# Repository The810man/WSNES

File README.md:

# WSNES „SNES-LoROM-Flashcart mit WLAN-Upload für Homebrew und Entwicklung auf echter Hardware.“

AI NOTICE: Hey so i use claude code for making my commits cleaner sometimes, also for release taggin. Code, pcb and CAD is hand made but also enhanced via mcp tools (for example checking routing and fixing issues like via placement etc.). Agentic workflows used for documentation and versioning.

WSNES is a SNES flash cartridge built around an **ESP32-S3** and parallel SRAM:

- The ESP loads a game from **microSD**, or one uploaded over **WiFi**, into SRAM.
- The SNES then reads that SRAM as a normal **LoROM** cartridge.
- Saves sit in a battery-backed SRAM and are backed up to the SD card.

The board uses the standard SNES cartridge PCB outline, so it fits a custom PAL / Super Famicom style housing.

## Status

**Latest release: [v0.3.2](https://github.com/The810man/WSNES/releases/tag/v0.3.2) (2026-11-17)**, with the gerbers and JLC files as release downloads. See [CHANGELOG.md](CHANGELOG.md).

| Part | State |
| --- | --- |
| Hardware v0.3 | Schematic done (ERC: 0 errors), all 90 parts placed, **fully routed, DRC clean** (KiCad 10.0.8: 0 errors, 0 unconnected, parity 0) |
| Production review | [2026-11-17](docs/reviews/2026-11-17_production-review.md): the tab-copper blocker and the missing USB ESD are **fixed and verified**. Every JLC line has an LCSC number. U1 and U13 were out of stock on 2026-11-17, and two bench checks are still open. See [`pcb/README.md`](pcb/README.md#before-ordering). |
| Production files | Gerbers in `pcb/production/jlc/`. JLC assembly as the full variant (`jlc/`) or the cheap prototype variant (`jlc-cheap/`, with a hand-assembly list) |
| Hardware v0.4 | In progress on `hw/v0.4`: schematic split into 9 sheets, U1/U5/U13 replaced by in-stock parts, two-sided placement, power pre-routed into the planes, net classes for hand routing. **Signal routing is being redone by hand.** See [`pcb/README.md`](pcb/README.md#routing-v04). |
| Housing | First draft: `cad/Cardridge.FCStd` (FreeCAD) |
| Firmware | Not in this repo yet |

## Repository layout

```
.
├── pcb/                    KiCad project (open WSNES_Proto.kicad_pro; the board needs KiCad 10)
│   ├── README.md           board details: who solders what, routing, ordering
│   ├── lib/                project symbols + footprints (cart edge drawn from scratch), vendor 3D models
│   ├── tools/              Python generators; design.py is the design table
│   ├── freerouting/        Specctra DSN for the autorouter
│   └── production/         full BOM, gerbers + JLCPCB assembly files (jlc/), cheap variant (jlc-cheap/)
├── cad/
│   ├── Cardridge.FCStd     first housing draft (FreeCAD)
│   ├── WSNES.step / .stl   latest KiCad 3D export of the board with all parts
│   └── WSNES_Proto.step / .stl   earlier export of the same board
├── docs/
│   ├── reviews/            design reviews (production review 2026-11-17)
│   ├── WSNES_Proto_schematic.pdf   schematic incl. bus map, GPIO map, firmware flow
│   └── masterplan.md               original architecture notes (German, historical)
├── analysis/               review evidence: deep_review.json + helper scripts (analyzer runs are not committed)
├── CHANGELOG.md            release history
├── LICENSES/               full licence texts
├── LICENSE.md              which licence covers what
└── CONTRIBUTING.md         terms for contributions
```

Start with [`pcb/README.md`](pcb/README.md) for the hardware.

## Tools

- KiCad 10 to open the board: `WSNES_Proto.kicad_pcb` is saved in KiCad 10 format, and KiCad 9 can't load it. The schematic still opens in KiCad 9.
- `kicad-cli` and the `pcbnew` Python module, for the generators in `pcb/tools/`
- freerouting, for autorouting
- Python 3

## Research references

These projects were studied while designing WSNES. None of their files are included here.

- [mrehkopf/sd2snes](https://github.com/mrehkopf/sd2snes): FPGA-based SNES flashcart
- [soniccd123/SNES-FeRAM-Cart](https://github.com/soniccd123/SNES-FeRAM-Cart): SNES cart with modern 3.3 V memory
- [MouseBiteLabs/Super-Nintendo-Cartridges](https://github.com/MouseBiteLabs/Super-Nintendo-Cartridges): open SNES cartridge PCBs

## Licence

WSNES is free for non-commercial use: it may be built, modified and shared, but selling it requires the author's permission.

- Hardware and docs: [CC BY-NC-SA 4.0](LICENSES/CC-BY-NC-SA-4.0.txt)
- Code: [PolyForm Noncommercial 1.0.0](LICENSES/PolyForm-Noncommercial-1.0.0.md)

See [LICENSE.md](LICENSE.md) for what counts as non-commercial, and [CONTRIBUTING.md](CONTRIBUTING.md) before sending changes.

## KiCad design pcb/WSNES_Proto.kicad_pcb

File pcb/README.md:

# WSNES Cart v0.4 (work in progress): mixed SMD/THT, two-sided, standard SNES PCB shape

v0.4 fits the standard SNES cartridge PCB outline: 112.2 × 66.7 mm plus the 11.1 mm contact tab, 1.2 mm thick, 4 layers. A custom housing can therefore look like a normal PAL / Super Famicom cartridge.

- **JLCPCB assembles all the small SMD parts, now on both sides.**
- **Hand-soldered after assembly:** the ESP module, the PIC, the battery holder, and the optional ICSP header.

**State on 2026-11-18:** the schematic is split into sheets, parts are re-sourced, and the board is re-placed on two sides with power pre-routed into the planes. **Signal routing is removed and has to be redone** (see [Routing](#routing-v04)). The gerbers in `production/jlc/` belong to the old, routed v0.3 board.

| | |
|---|---|
| Schematic | `WSNES_Proto.kicad_sch` (root overview) + 9 sheets: `edge_cic`, `snes_buffers`, `rom_glue`, `esp_serial`, `level_reset`, `esp32`, `microsd`, `power_usb`, `save_ram`. ERC: 0 errors. All 600 pins checked against the design table. |
| PCB | `WSNES_Proto.kicad_pcb`: 92 parts placed (49 top, 43 bottom), power fanned out into the planes, signals unrouted. DRC (KiCad 10.0.8): 0 errors, schematic parity 0, 268 unconnected pads left to route. |
| Routing input | `freerouting/WSNES_Proto.dsn` (In1/In2 exported as power planes, so freerouting stays on F.Cu / B.Cu) |
| JLC assembly | `production/jlc/WSNES_BOM_JLC.csv` + `production/jlc/WSNES_CPL_JLC.csv` (only the parts JLC solders, top and bottom) |
| Full BOM | `production/WSNES_Proto_BOM.csv` (the `Assembly` column says who solders what) |
| Cheap prototype | `production/jlc-cheap/`: smaller JLC bill. JLC leaves off U1 (low stock), SW1, SW2 and U23, and the LEDs are all red basic parts. Includes a hand-assembly list. See its README. |
| 3D model | `../cad/WSNES_Proto.step` / `.stl` are still the v0.3 export. Re-export after routing: the back now carries parts, about 1 mm high. |
| Schematic PDF | `../docs/WSNES_Proto_schematic.pdf` |

## DRC status

0 errors, schematic parity 0, 268 unconnected pads (the signal routing). The warnings are reviewed and harmless:

- **`silk_overlap` / `silk_over_copper` (about 90):** silkscreen of the small back-side passives touching each other or their pads. Their references are hidden, and the fab clips silk on pads.
- **`silk_edge_clearance` ×2 (U21):** the ESP32 module outline overhangs the top edge by design, because the antenna sits at the edge. The fab clips silk there.
- **`lib_footprint_mismatch` (J2, J5):** these were placed from the KiCad 9 library. The KiCad 10 copies have identical pad geometry but name the shield pads `SH` (this project uses `S1`/`11` to match its symbols), and J5's pads are roundrect. Do **not** "update from library": it would renumber the shield pads. ERC shows the matching `lib_symbol_mismatch` warnings.

Project rules in `WSNES_Proto.kicad_dru`:

- **No tracks on In1 / In2.** Both are "power" layers (planes only). Reach a plane with a via.
- **Power tracks at least 0.3 mm** (the net class default is 0.5 mm).
- **SMD IC GND pins** (all `U*` except the hand-soldered ESP U21) connect solidly to the GND pours.
- **USB pair:** gap 0.18–0.3 mm, skew at most 1 mm.
- **Via floor 0.45/0.2 mm.** Signals default to 0.5/0.25, power to 0.6/0.3.

Four `tab_no_pour` rule areas (F.Cu, In1, In2, B.Cu; x 119–181, y ≥ 156) keep every pour out of the gold-finger band and the bevelled tip. The GND and +5V fingers (5/36, 27/58) have their own 0.8 mm stubs and two vias each just above the fingers, because the pour does not reach them. Two small `no_pour_sliver` keepouts on In2 (around x 158–166, y 152–155) remove thin, unconnected slivers of the +5V plane.

**In2 split (v0.4):** +3V3 covers the top band (USB, LDO, microSD; y < 101–105.5) and the ESP column (x > 171, y < 113.3). +5V covers everything else and now reaches up under both SRAMs, so U1's VCC pin, D1, D4 and U20 sit over +5V. U14 (CD74HC4050, the only 3.3 V chip in the 5 V area) and its cap C17 get their +3V3 through one short track.

## Assembly split

| Hand-soldered (`HAND`) | JLC (`JLC`), top | JLC (`JLC`), bottom |
|---|---|---|
| U21 ESP32-S3-WROOM-1-N16R8. Solder the castellated edge pads; the centre GND pad is optional, since pins 1 and 40 are GND too. | 74xx logic except U2, both SRAMs, regulator, diodes, FET, MCP100, microSD socket, USB-C with U23, buttons, LEDs, bulk caps, microSD pull-ups, CC resistors | U2 (A0–A7 buffer, right above the B-side fingers), every 100 nF decoupling cap except C18, the control-line pull-ups and series resistors (R1, R3, R6–R16, R25, R26, R28, R29), C22 |
| U15 PIC12F629 (DIP-8), flashed with the SuperCIC key firmware, ideally beforehand | | |
| BT1 CR2032 holder (THT) | | |
| J3 ICSP header: optional, only for flashing the PIC in place | | |

Parts on both sides need **JLC Standard PCBA with two-sided assembly**. Economic PCBA is top-side only. The second side adds a setup fee to the quote.

## What changed vs. v0.2 (the circuit is the same, the packages are smaller)

- **ESP:** DevKitC-1 → bare **ESP32-S3-WROOM-1 module**. The board now carries what the DevKit used to provide:
  - AP2112K-3.3 regulator
  - USB-C on the native USB pins (GPIO19/20) for flashing and the serial console
  - BOOT and RESET buttons, plus a status LED on GPIO48
- **microSD:** the plug-in module became a push-push socket at 3.3 V with pull-ups. Card detect is on GPIO38.
- **DIP → SMD:**
  - 74xx logic → TSSOP
  - AS6C4008 / AS6C1008 → SOP-32 (same pinout)
  - 2N7000 → 2N7002 (different pin order; the netlist is already remapped)
  - MCP100 → SOT-23, BAT85 ×2 → BAT54C, the bussed SIP resistor network → 8 × 0603
- **Removed:** the SD VCC jumper and the EXP header.
- **4 layers:**
  - In1 = GND plane.
  - In2 = +3V3 in the top strip (ESP, SD, regulator) and +5V below it (logic, SRAMs, PIC).
  - Top and bottom layers get GND pours after routing.

GPIO numbers are the same as before, so firmware written for v0.2 still applies. New pins: GPIO0 BOOT, GPIO38 SD card detect, GPIO48 LED, GPIO19/20 USB.

## Housing cutouts (top edge)

Distances are measured from the board's left edge, with the label side facing the viewer.

| Feature | Position | Notes |
|---|---|---|
| microSD slot | centre 21.5 mm | the card sticks out above the top edge |
| USB-C | centre 62.5 mm | about 9 × 3.5 mm opening |
| ESP antenna | 85.5–103.5 mm | plastic is fine; no cutout strictly needed |
| Contact tab | centre 58.5 mm | |

The tallest parts are the PIC (DIP-8, about 4.5 mm without a socket) and the CR2032 holder (about 6 mm). `../cad/WSNES_Proto.step` can be loaded into a CAD tool to check them against the shell.

**The outline should be verified against an original cart with calipers before a housing is built.** It follows the standard Nintendo SNES PCB shape (body width, corner steps, side notches). If a PAL shell has posts in different places, please open an issue with the measurements. The outline is `OUTLINE` in `tools/gen_pcb.py`.

## Routing (v0.4)

The v0.3 routing came from freerouting: long detours, 3.9 m of signal on the inner planes, and odd tree shapes. For v0.4 all signal routing was removed. What is already done:

- **Power is finished.** Every SMD pad on GND, +5V or +3V3 has a short stub and a via into its plane (125 vias). THT pads reach the planes directly. Only U14 pin 1 and C17 pin 1 (+3V3) still need a short track. So the ratsnest now shows signals only, with no more "resistor to resistor" lines on the supply nets.
- **Decoupling caps are on the back, under their IC,** tied to the IC's supply via. Do not move them away.
- **Net classes colour the ratsnest** (View → Net colour mode: Ratsnest): red = Power, purple = USB, orange = Clock, blue = AddrBus (SA*, SNES_A*, SV_A*, EA19), green = DataBus (SD0–7, SNES_D0–7), grey = everything else.
- **Track widths and vias come from the net class.** Leave the width box on "use net class" (first entry), or cycle with W / Shift+W: 0.15, 0.2, 0.25, 0.3, 0.4, 0.5, 0.8 mm. Vias: 0.45/0.2, 0.5/0.25, 0.6/0.3, 0.8/0.4.

Why the ratsnest connected resistors to resistors: KiCad draws the shortest tree between all pads of a net. Ten pull-ups on +3V3 are one net, so their +3V3 pads got chained together. With the supplies now done through vias, those lines are gone. On a signal net with several loads (BUS_ESP goes to the ESP, a pull-up and 8 gate inputs), any tree is electrically correct. The ratsnest only suggests the shortest one; the net can be routed in any order.

### Suggested order

1. **USB** (purple): J5 → U23 → U21 pins 13/14, with the diff-pair router (key 6) on F.Cu.
2. **Clocks** (orange): SR_SCK and SR_LATCH from R28/R29 as one daisy chain along U9 → U10 → U11 → U12 → U13. Keep them short and away from the data bus.
3. **SNES edge to the buffers:** U2 is on the back right above fingers 10–17, so A0–A7 go straight on B.Cu with no via. U3, U4, U5 and U17 take the F-side fingers.
4. **Buses** (blue / green): SA* and SD* run between the buffers, the shift registers and both SRAMs. Use **F.Cu mostly horizontal and B.Cu mostly vertical**, and change layer with a via. That convention keeps crossings cheap.
5. **The rest** (grey), then the U14 / C17 +3V3 track.
6. Press B to refill the zones, then run DRC.

### Interactive router settings (Route → Interactive Router Settings)

These are KiCad user settings, not project settings, so they are not stored in the repository:

- **Mode: Shove** rather than Walk around. Shove pushes neighbouring tracks aside, which suits a dense bus board.
- Optimizer effort **High**. Enable *Smooth dragged segments*, *Remove redundant tracks* and *Smart pads*.
- *Allow DRC violations*: off.
- Useful keys: X route, 6 diff pair, V via while routing, / switch posture, D drag, L lock.

### Using freerouting

`freerouting/WSNES_Proto.dsn` now declares In1/In2 as power planes, so freerouting stays on the two outer layers. Route USB, the clocks and the edge-connector fan-out by hand first and **lock** them (L): locked tracks are exported as fixed wiring. Then:

    java -jar freerouting-2.5.0.jar -de freerouting/WSNES_Proto.dsn -do freerouting/WSNES_Proto.ses -mp 100

Import with **File → Import → Specctra Session**. Expect to clean up by hand.

### JLC order options

- 4 layers, **1.2 mm**, ENIG
- gold fingers with **45° bevel**
- assembly: **both sides**, using the two files in `production/jlc/`. Check rotations in JLC's placement preview on both sides. SOT-23 / SOT-23-5 / SOT-23-6 parts often need 180°, and bottom-side parts are shown mirrored.

## Save RAM (unchanged from v0.2)

- U16 is battery-backed and mapped to LoROM `$70-$7D:0000-7FFF`.
  - Since 2026-11-17 it is a CY62128ELL-45SXI (`C2953613`), because the AS6C1008-55SIN was out of stock. Same pinout and SOP-32 footprint.
  - The CY62128E is rated 4.5–5.5 V, but VSAVE is one BAT54C drop (≈ 0.35 V) below +5V, so it is only in spec while the console delivers about 4.9 V or more. Go back to the AS6C1008 (2.7–5.5 V) when it is in stock.
- U17 74HCT138 decodes the save area.
- U19 masks the size to match the ROM header.
- U20 MCP100 blocks writes below about 4.4 V.

The ESP copies the save to `<game>.srm` on SD on return to the menu or on reset. If the console is switched off mid-game, the battery keeps the save, and the ESP backs it up at the next power-up.

## Before ordering

Stock was checked on 2026-11-18 against the LCSC catalogue, which feeds JLC assembly:

- **Replaced, because the old parts were at 0:**
  - U1 AS6C4008-55SIN → **CY62148ELL-55SXI** (`C2953576`): same JEDEC pinout and 450-mil SOIC-32 land pattern, 4.5–5.5 V, 55 ns. Only **5** were in stock: order early, or source it separately and hand-solder it (the cheap variant does that).
  - U5 74AHCT245PW → **TI SN74AHCT245PWR** (`C10910`), same pinout.
  - U13 74HCT165PW → **TI SN74HCT165PWR** (`C3304572`), same pinout, still HCT.
- **Low but enough for a prototype:** U21 ESP32-S3-WROOM-1-N16R8 (11 in stock), U15 PIC12F629-I/P (12), U16 CY62128ELL-45SXI (63). U21 and U15 are hand-soldered anyway.
- **Everything else** is in stock in the thousands.
- JLC's parts page has the final word on stock at order time.

Still open from the 2026-11-17 production review:

- **Bench checks:**
  - Edge pinout: check continuity against an original cart. The finger at x = 177.5 (pin 5/36) must be GND on the same face.
  - Console /RESET driver: Q1 pulls pin 26 low by default. Measure whether the console drives that line push-pull before relying on it.
- **U16 supply:** the CY62128E is rated 4.5–5.5 V, and VSAVE is one BAT54C drop below +5V. Go back to the AS6C1008 (2.7–5.5 V) when it is in stock.
- **SNES 5 V budget:** ESP32 WiFi peaks reach about 350–500 mA. Lowering the TX power helps if the console struggles.
- **Timing:** SlowROM games have margin. FastROM games are marginal with HCT glue; AHCT versions of the glue chips would help.
- **USB-only power** (no console): only the ESP, SD and 3.3 V side is powered. The firmware must not drive the 5 V logic while `SNES_5V_SENSE = 0`. Also, the 10 k pull-ups R10–R16 go to +3V3 and feed the unpowered 5 V logic through its input clamp diodes (about 0.3 mA each). That is harmless, but it lifts the dead +5V rail a little.

## Bus map, GPIO map, firmware flow

These are unchanged from v0.2 and documented on the schematic sheet (`../docs/WSNES_Proto_schematic.pdf`):

- **Bus ownership:** a single `BUS_ESP` GPIO, pulled high, so the ESP owns the bus at power-up.
- **Shift word:** 32 bits, MSB first: `[DATA, A23..16 (A19 = save-chip select), A15..8, A7..0]`.

## Regenerate

Run these from `pcb/`.

```
python3 tools/gen_project.py .        # libraries + hierarchical schematic + net classes from tools/design.py
kicad-cli sch export netlist --format kicadsexpr -o /tmp/p.net WSNES_Proto.kicad_sch
python3 tools/verify_netlist.py /tmp/p.net tools/intended_pins.json
kicad-cli sch erc WSNES_Proto.kicad_sch

# after a schematic change: in KiCad, Tools -> Update PCB from Schematic (F8). Footprints are linked by path.
# tools/board_v04.py was the one-shot v0.4 conversion (rip-up, two-sided placement, power fan-out).
# Do not rerun it on a routed board: it removes all routing.
python3 tools/gen_pcb.py .            # DO NOT RUN: rebuilds the PCB from scratch and discards the placement

# production files
python3 tools/export_bom.py .
python3 tools/export_cheap.py .
kicad-cli sch export pdf -o ../docs/WSNES_Proto_schematic.pdf WSNES_Proto.kicad_sch
kicad-cli pcb export step -f -o ../cad/WSNES_Proto.step WSNES_Proto.kicad_pcb

# refill zones + full check
kicad-cli pcb drc --refill-zones --save-board --schematic-parity WSNES_Proto.kicad_pcb
```

`gen_project.py` updates only the net classes, the track/via presets and the rule minimums in `WSNES_Proto.kicad_pro`. Everything else set in KiCad (zone defaults, ERC map, plot settings) is kept.

BT1, J5 and U1/U16 use vendor models from `lib/3dmodels/`, because KiCad's 3D library has none for those footprints. See `lib/3dmodels/README.md` for where they come from and their offsets.

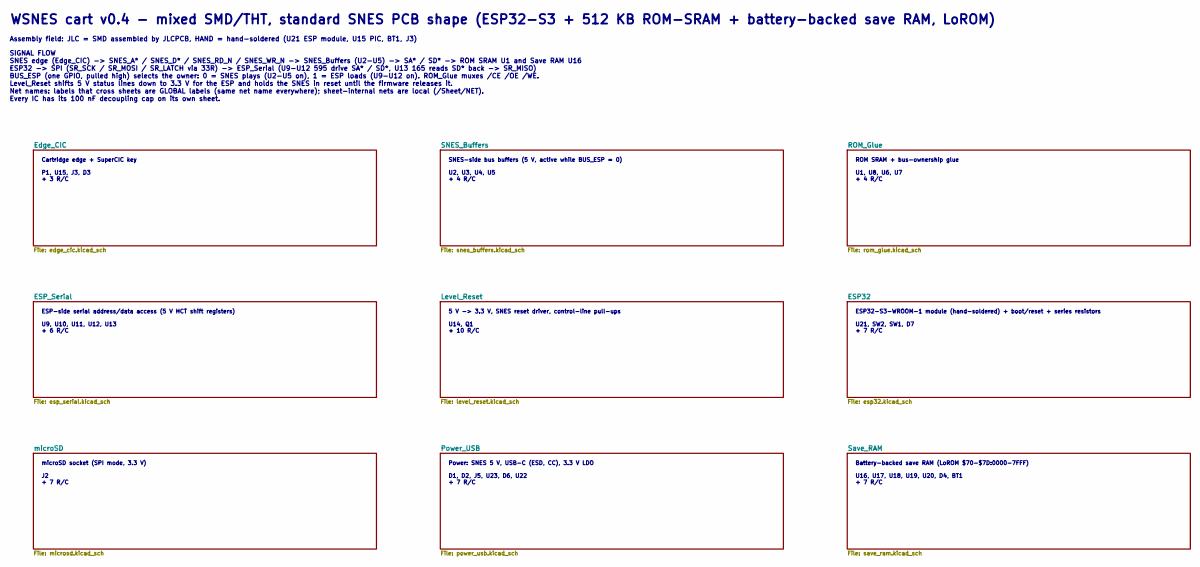
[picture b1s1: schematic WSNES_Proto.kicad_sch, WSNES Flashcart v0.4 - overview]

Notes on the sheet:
WSNES cart v0.4 - mixed SMD/THT, standard SNES PCB shape (ESP32-S3 + 512 KB ROM-SRAM + battery-backed save RAM, LoROM)
Assembly field: JLC = SMD assembled by JLCPCB, HAND = hand-soldered (U21 ESP module, U15 PIC, BT1, J3)
SIGNAL FLOW SNES edge (Edge_CIC) -> SNES_A* / SNES_D* / SNES_RD_N / SNES_WR_N -> SNES_Buffers (U2-U5) -> SA* / SD* -> ROM SRAM U1 and Save RAM U16 ESP32 -> SPI (SR_SCK / SR_MOSI / SR_LATCH via 33R) -> ESP_Serial (U9-U12 595 drive SA* / SD*, U13 165 reads SD* back -> SR_MISO) BUS_ESP (one GPIO, pull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
Cartridge edge + SuperCIC key P1, U15, J3, D3 + 3 R/C
SNES-side bus buffers (5 V, active while BUS_ESP = 0) U2, U3, U4, U5 + 4 R/C
ROM SRAM + bus-ownership glue U1, U8, U6, U7 + 4 R/C
ESP-side serial address/data access (5 V HCT shift registers) U9, U10, U11, U12, U13 + 6 R/C
5 V -> 3.3 V, SNES reset driver, control-line pull-ups U14, Q1 + 10 R/C
ESP32-S3-WROOM-1 module (hand-soldered) + boot/reset + series resistors U21, SW2, SW1, D7 + 7 R/C
microSD socket (SPI mode, 3.3 V) J2 + 7 R/C
Power: SNES 5 V, USB-C (ESD, CC), 3.3 V LDO D1, D2, J5, U23, D6, U22 + 7 R/C
Battery-backed save RAM (LoROM $70-$7D:0000-7FFF) U16, U17, U18, U19, U20, D4, BT1 + 7 R/C

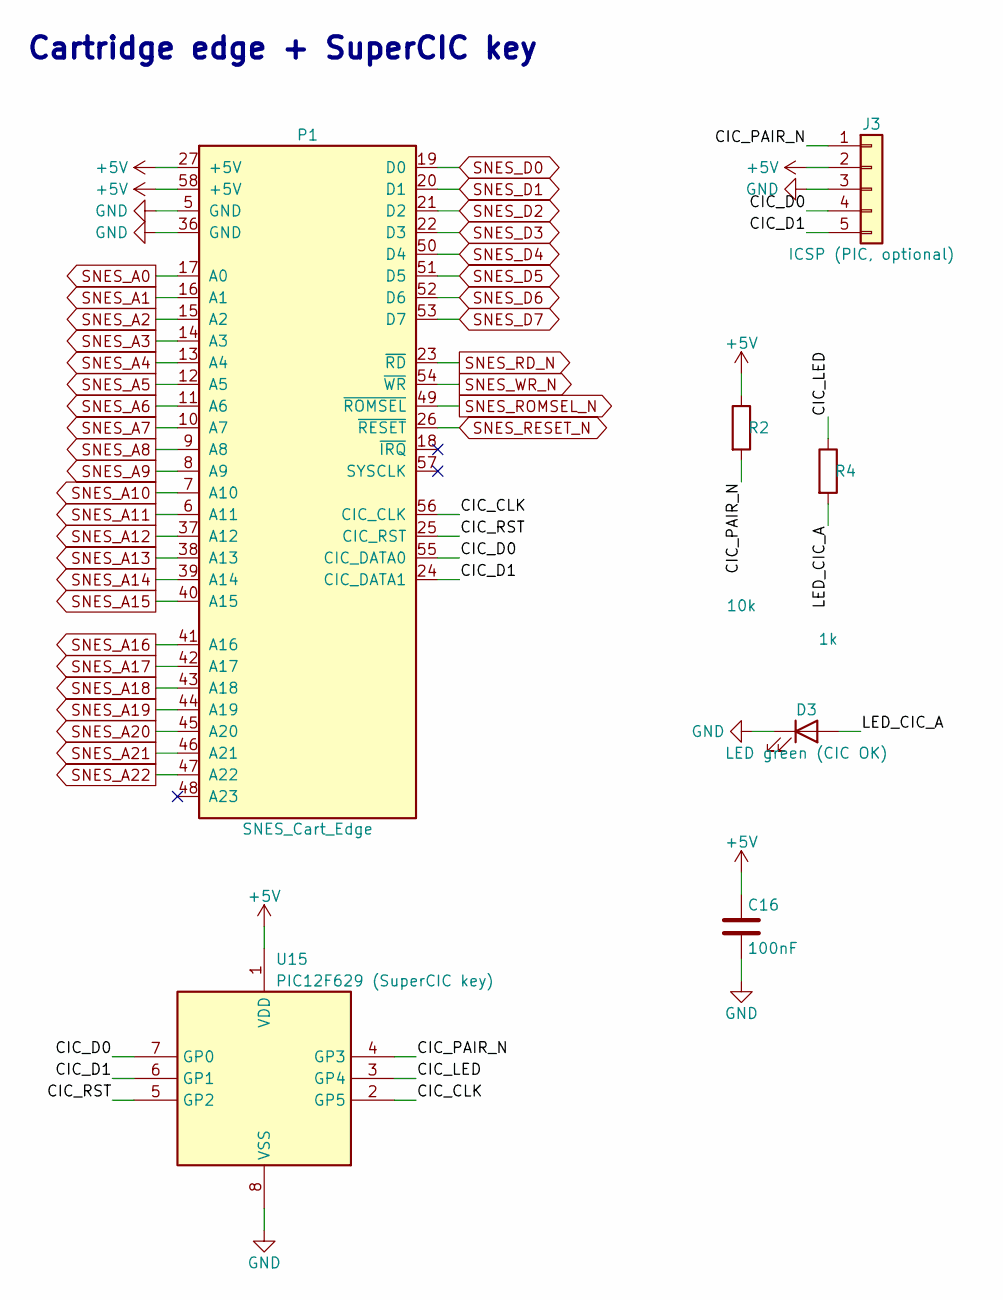
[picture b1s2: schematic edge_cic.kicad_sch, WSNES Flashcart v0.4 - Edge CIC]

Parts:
C16: 100nF; C_0603_1608Metric; MPN CC0603KRX7R9BB104; LCSC C14663
D3: LED green (CIC OK); LED_0603_1608Metric; MPN KT-0603G; LCSC C12624
J3: ICSP (PIC, optional); PinHeader_1x05_P2.54mm_Vertical; MPN DM254R-11-05-85; LCSC C2935976
P1: SNES_Cart_Edge; SNES_Cart_Edge_46P_P2.50mm
R2: 10k; R_0603_1608Metric; MPN 0603WAF1002T5E; LCSC C25804
R4: 1k; R_0603_1608Metric; MPN 0603WAF1001T5E; LCSC C21190
U15: PIC12F629 (SuperCIC key); DIP-8_W7.62mm; MPN PIC12F629-I/P; LCSC C9785

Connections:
+5V: C16.1, J3.2, P1.27 (+5V), P1.58 (+5V), R2.1, U15.1 (VDD); also elsewhere on the board
/Edge_CIC/CIC_CLK: P1.56 (CIC_CLK), U15.2 (GP5)
/Edge_CIC/CIC_D0: J3.4, P1.55 (CIC_DATA0), U15.7 (GP0)
/Edge_CIC/CIC_D1: J3.5, P1.24 (CIC_DATA1), U15.6 (GP1)
/Edge_CIC/CIC_LED: R4.1, U15.3 (GP4)
/Edge_CIC/CIC_PAIR_N: J3.1, R2.2, U15.4 (GP3)
/Edge_CIC/CIC_RST: P1.25 (CIC_RST), U15.5 (GP2)
/Edge_CIC/LED_CIC_A: D3.2 (A), R4.2
GND: C16.2, D3.1 (K), J3.3, P1.5 (GND), P1.36 (GND), U15.8 (VSS); also elsewhere on the board
SNES_A0: P1.17 (A0); also elsewhere on the board
SNES_A1: P1.16 (A1); also elsewhere on the board
SNES_A2: P1.15 (A2); also elsewhere on the board
SNES_A3: P1.14 (A3); also elsewhere on the board
SNES_A4: P1.13 (A4); also elsewhere on the board
SNES_A5: P1.12 (A5); also elsewhere on the board
SNES_A6: P1.11 (A6); also elsewhere on the board
SNES_A7: P1.10 (A7); also elsewhere on the board
SNES_A8: P1.9 (A8); also elsewhere on the board
SNES_A9: P1.8 (A9); also elsewhere on the board
SNES_A10: P1.7 (A10); also elsewhere on the board
SNES_A11: P1.6 (A11); also elsewhere on the board
SNES_A12: P1.37 (A12); also elsewhere on the board
SNES_A13: P1.38 (A13); also elsewhere on the board
SNES_A14: P1.39 (A14); also elsewhere on the board
SNES_A15: P1.40 (A15); also elsewhere on the board
SNES_A16: P1.41 (A16); also elsewhere on the board
SNES_A17: P1.42 (A17); also elsewhere on the board
SNES_A18: P1.43 (A18); also elsewhere on the board
SNES_A19: P1.44 (A19); also elsewhere on the board
SNES_A20: P1.45 (A20); also elsewhere on the board
SNES_A21: P1.46 (A21); also elsewhere on the board
SNES_A22: P1.47 (A22); also elsewhere on the board
SNES_D0: P1.19 (D0); also elsewhere on the board
SNES_D1: P1.20 (D1); also elsewhere on the board
SNES_D2: P1.21 (D2); also elsewhere on the board
SNES_D3: P1.22 (D3); also elsewhere on the board
SNES_D4: P1.50 (D4); also elsewhere on the board
SNES_D5: P1.51 (D5); also elsewhere on the board
SNES_D6: P1.52 (D6); also elsewhere on the board
SNES_D7: P1.53 (D7); also elsewhere on the board
SNES_RD_N: P1.23 (~RD); also elsewhere on the board
SNES_RESET_N: P1.26 (~RESET); also elsewhere on the board
SNES_ROMSEL_N: P1.49 (~ROMSEL); also elsewhere on the board
SNES_WR_N: P1.54 (~WR); also elsewhere on the board

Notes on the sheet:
Cartridge edge + SuperCIC key

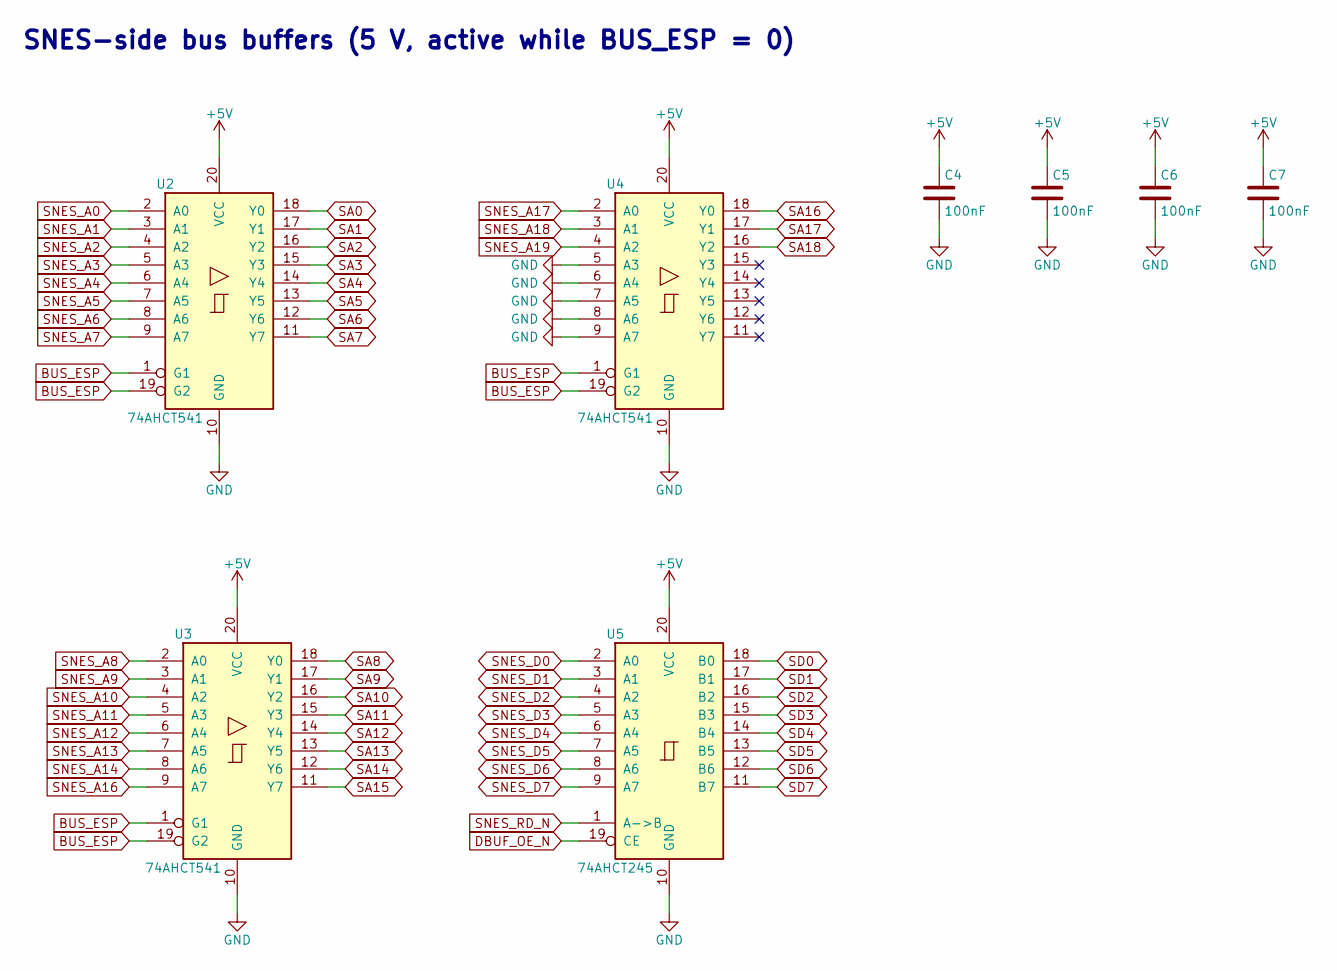
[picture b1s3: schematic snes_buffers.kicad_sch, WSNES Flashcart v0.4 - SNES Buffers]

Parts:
C4, C5, C6, C7: 100nF; C_0603_1608Metric; MPN CC0603KRX7R9BB104; LCSC C14663
U2, U3, U4: 74AHCT541; TSSOP-20_4.4x6.5mm_P0.65mm; MPN 74AHCT541PW,118; LCSC C84548
U5: 74AHCT245; TSSOP-20_4.4x6.5mm_P0.65mm; MPN SN74AHCT245PWR; LCSC C10910

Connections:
+5V: C4.1, C5.1, C6.1, C7.1, U2.20 (VCC), U3.20 (VCC), U4.20 (VCC), U5.20 (VCC); also elsewhere on the board
BUS_ESP: U2.1 (G1), U2.19 (G2), U3.1 (G1), U3.19 (G2), U4.1 (G1), U4.19 (G2); also elsewhere on the board
DBUF_OE_N: U5.19 (CE); also elsewhere on the board
GND: C4.2, C5.2, C6.2, C7.2, U2.10 (GND), U3.10 (GND), U4.5 (A3), U4.6 (A4), U4.7 (A5), U4.8 (A6), U4.9 (A7), U4.10 (GND), U5.10 (GND); also elsewhere on the board
SA0: U2.18 (Y0); also elsewhere on the board
SA1: U2.17 (Y1); also elsewhere on the board
SA2: U2.16 (Y2); also elsewhere on the board
SA3: U2.15 (Y3); also elsewhere on the board
SA4: U2.14 (Y4); also elsewhere on the board
SA5: U2.13 (Y5); also elsewhere on the board
SA6: U2.12 (Y6); also elsewhere on the board
SA7: U2.11 (Y7); also elsewhere on the board
SA8: U3.18 (Y0); also elsewhere on the board
SA9: U3.17 (Y1); also elsewhere on the board
SA10: U3.16 (Y2); also elsewhere on the board
SA11: U3.15 (Y3); also elsewhere on the board
SA12: U3.14 (Y4); also elsewhere on the board
SA13: U3.13 (Y5); also elsewhere on the board
SA14: U3.12 (Y6); also elsewhere on the board
SA15: U3.11 (Y7); also elsewhere on the board
SA16: U4.18 (Y0); also elsewhere on the board
SA17: U4.17 (Y1); also elsewhere on the board
SA18: U4.16 (Y2); also elsewhere on the board
SD0: U5.18 (B0); also elsewhere on the board
SD1: U5.17 (B1); also elsewhere on the board
SD2: U5.16 (B2); also elsewhere on the board
SD3: U5.15 (B3); also elsewhere on the board
SD4: U5.14 (B4); also elsewhere on the board
SD5: U5.13 (B5); also elsewhere on the board
SD6: U5.12 (B6); also elsewhere on the board
SD7: U5.11 (B7); also elsewhere on the board
SNES_A0: U2.2 (A0); also elsewhere on the board
SNES_A1: U2.3 (A1); also elsewhere on the board
SNES_A2: U2.4 (A2); also elsewhere on the board
SNES_A3: U2.5 (A3); also elsewhere on the board
SNES_A4: U2.6 (A4); also elsewhere on the board
SNES_A5: U2.7 (A5); also elsewhere on the board
SNES_A6: U2.8 (A6); also elsewhere on the board
SNES_A7: U2.9 (A7); also elsewhere on the board
SNES_A8: U3.2 (A0); also elsewhere on the board
SNES_A9: U3.3 (A1); also elsewhere on the board
SNES_A10: U3.4 (A2); also elsewhere on the board
SNES_A11: U3.5 (A3); also elsewhere on the board
SNES_A12: U3.6 (A4); also elsewhere on the board
SNES_A13: U3.7 (A5); also elsewhere on the board
SNES_A14: U3.8 (A6); also elsewhere on the board
SNES_A16: U3.9 (A7); also elsewhere on the board
SNES_A17: U4.2 (A0); also elsewhere on the board
SNES_A18: U4.3 (A1); also elsewhere on the board
SNES_A19: U4.4 (A2); also elsewhere on the board
SNES_D0: U5.2 (A0); also elsewhere on the board
SNES_D1: U5.3 (A1); also elsewhere on the board
SNES_D2: U5.4 (A2); also elsewhere on the board
SNES_D3: U5.5 (A3); also elsewhere on the board
SNES_D4: U5.6 (A4); also elsewhere on the board
SNES_D5: U5.7 (A5); also elsewhere on the board
SNES_D6: U5.8 (A6); also elsewhere on the board
SNES_D7: U5.9 (A7); also elsewhere on the board
SNES_RD_N: U5.1 (A->B); also elsewhere on the board

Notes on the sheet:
SNES-side bus buffers (5 V, active while BUS_ESP = 0)

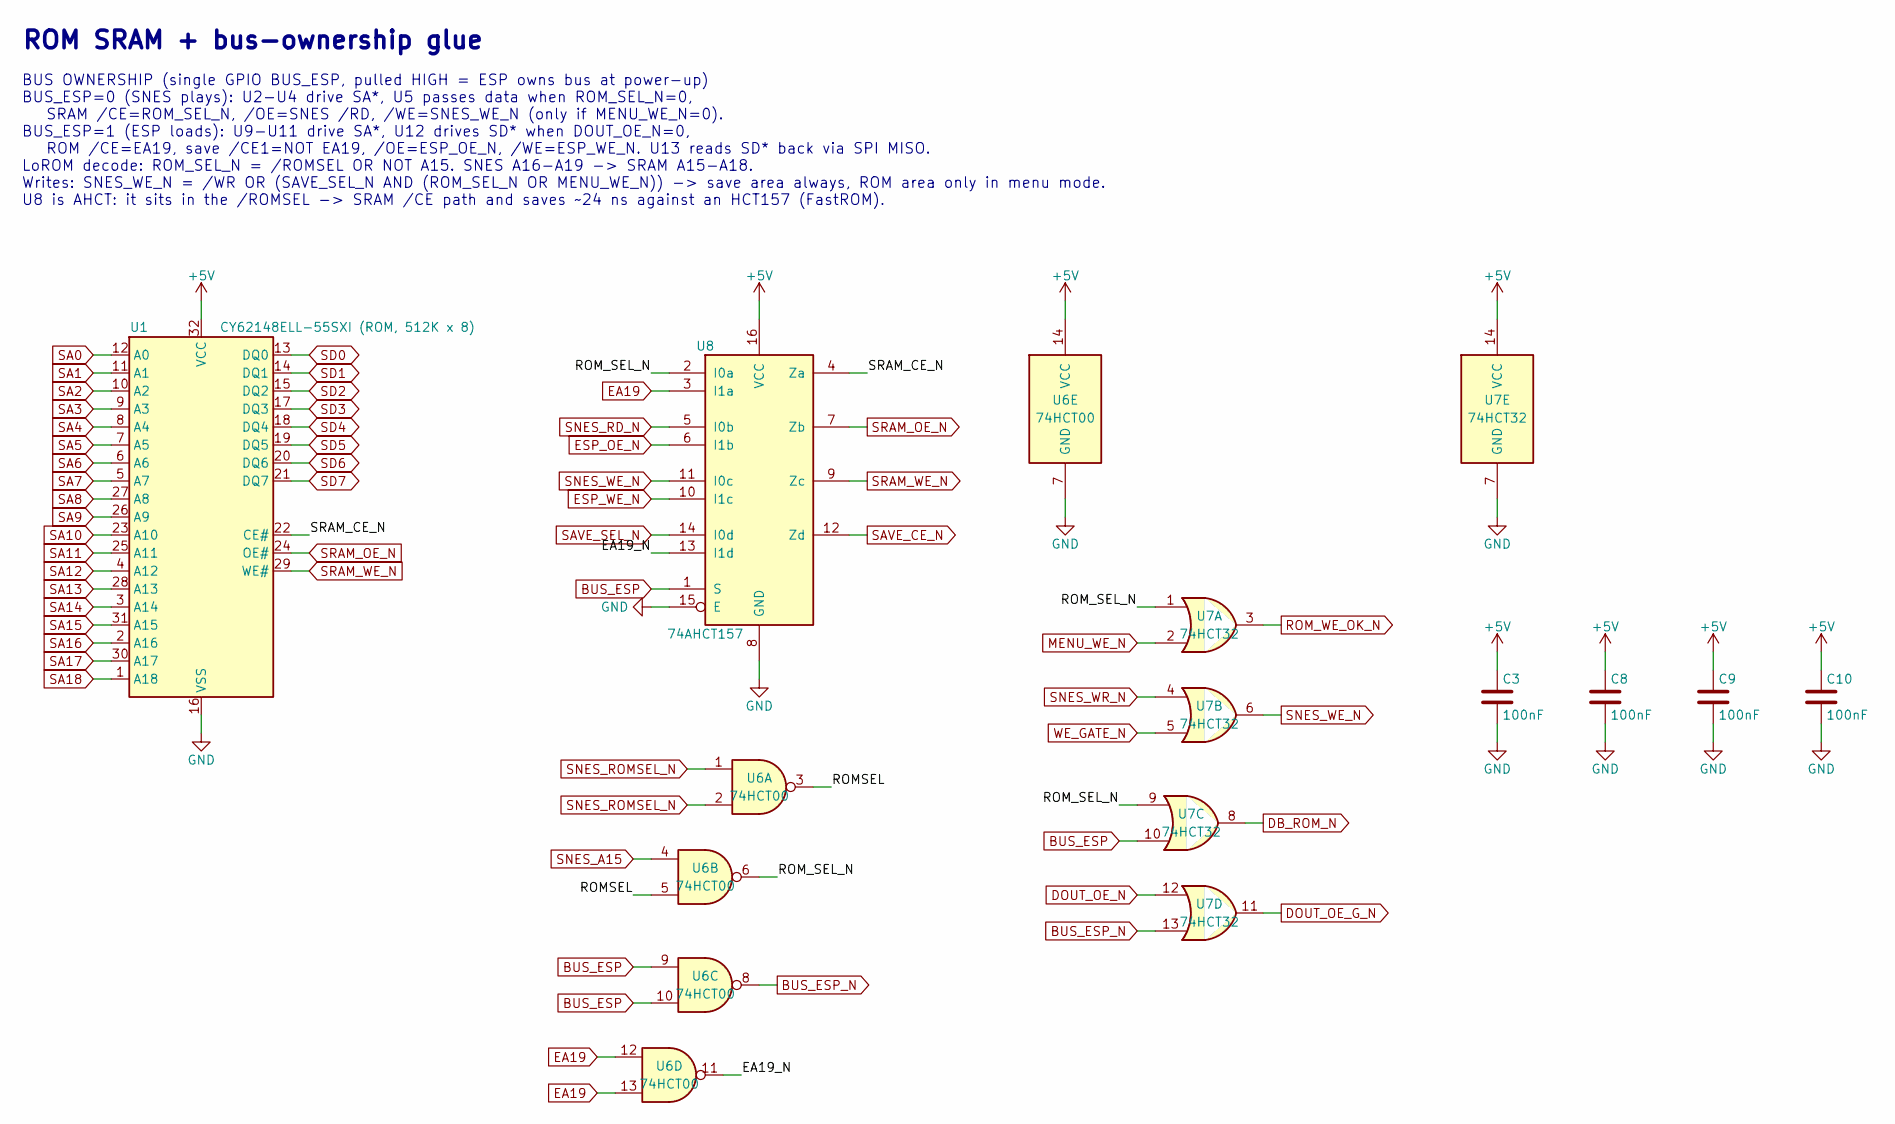
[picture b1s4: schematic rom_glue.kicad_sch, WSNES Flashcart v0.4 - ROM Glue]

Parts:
C3, C8, C9, C10: 100nF; C_0603_1608Metric; MPN CC0603KRX7R9BB104; LCSC C14663
U1: CY62148ELL-55SXI (ROM, 512K x 8); SOP-32_11.305x20.495mm_P1.27mm; MPN CY62148ELL-55SXI; LCSC C2953576
U6: 74HCT00; TSSOP-14_4.4x5mm_P0.65mm; MPN 74HCT00PW,118; LCSC C8206
U7: 74HCT32; TSSOP-14_4.4x5mm_P0.65mm; MPN SN74HCT32PWR; LCSC C132266
U8: 74AHCT157; TSSOP-16_4.4x5mm_P0.65mm; MPN SN74AHCT157PWR; LCSC C2674471

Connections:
+5V: C3.1, C8.1, C9.1, C10.1, U1.32 (VCC), U6.14 (VCC), U7.14 (VCC), U8.16 (VCC); also elsewhere on the board
/ROM_Glue/EA19_N: U6.11, U8.13 (I1d)
/ROM_Glue/ROMSEL: U6.3, U6.5
/ROM_Glue/ROM_SEL_N: U6.6, U7.1, U7.9, U8.2 (I0a)
/ROM_Glue/SRAM_CE_N: U1.22 (CE#), U8.4 (Za)
BUS_ESP: U6.9, U6.10, U7.10, U8.1 (S); also elsewhere on the board
BUS_ESP_N: U6.8, U7.13; also elsewhere on the board
DB_ROM_N: U7.8; also elsewhere on the board
DOUT_OE_G_N: U7.11; also elsewhere on the board
DOUT_OE_N: U7.12; also elsewhere on the board
EA19: U6.12, U6.13, U8.3 (I1a); also elsewhere on the board
ESP_OE_N: U8.6 (I1b); also elsewhere on the board
ESP_WE_N: U8.10 (I1c); also elsewhere on the board
GND: C3.2, C8.2, C9.2, C10.2, U1.16 (VSS), U6.7 (GND), U7.7 (GND), U8.8 (GND), U8.15 (E); also elsewhere on the board
MENU_WE_N: U7.2; also elsewhere on the board
ROM_WE_OK_N: U7.3; also elsewhere on the board
SA0: U1.12 (A0); also elsewhere on the board
SA1: U1.11 (A1); also elsewhere on the board
SA2: U1.10 (A2); also elsewhere on the board
SA3: U1.9 (A3); also elsewhere on the board
SA4: U1.8 (A4); also elsewhere on the board
SA5: U1.7 (A5); also elsewhere on the board
SA6: U1.6 (A6); also elsewhere on the board
SA7: U1.5 (A7); also elsewhere on the board
SA8: U1.27 (A8); also elsewhere on the board
SA9: U1.26 (A9); also elsewhere on the board
SA10: U1.23 (A10); also elsewhere on the board
SA11: U1.25 (A11); also elsewhere on the board
SA12: U1.4 (A12); also elsewhere on the board
SA13: U1.28 (A13); also elsewhere on the board
SA14: U1.3 (A14); also elsewhere on the board
SA15: U1.31 (A15); also elsewhere on the board
SA16: U1.2 (A16); also elsewhere on the board
SA17: U1.30 (A17); also elsewhere on the board
SA18: U1.1 (A18); also elsewhere on the board
SAVE_CE_N: U8.12 (Zd); also elsewhere on the board
SAVE_SEL_N: U8.14 (I0d); also elsewhere on the board
SD0: U1.13 (DQ0); also elsewhere on the board
SD1: U1.14 (DQ1); also elsewhere on the board
SD2: U1.15 (DQ2); also elsewhere on the board
SD3: U1.17 (DQ3); also elsewhere on the board
SD4: U1.18 (DQ4); also elsewhere on the board
SD5: U1.19 (DQ5); also elsewhere on the board
SD6: U1.20 (DQ6); also elsewhere on the board
SD7: U1.21 (DQ7); also elsewhere on the board
SNES_A15: U6.4; also elsewhere on the board
SNES_RD_N: U8.5 (I0b); also elsewhere on the board
SNES_ROMSEL_N: U6.1, U6.2; also elsewhere on the board
SNES_WE_N: U7.6, U8.11 (I0c); also elsewhere on the board
SNES_WR_N: U7.4; also elsewhere on the board
SRAM_OE_N: U1.24 (OE#), U8.7 (Zb); also elsewhere on the board
SRAM_WE_N: U1.29 (WE#), U8.9 (Zc); also elsewhere on the board
WE_GATE_N: U7.5; also elsewhere on the board

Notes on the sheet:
ROM SRAM + bus-ownership glue
BUS OWNERSHIP (single GPIO BUS_ESP, pulled HIGH = ESP owns bus at power-up) BUS_ESP=0 (SNES plays): U2-U4 drive SA*, U5 passes data when ROM_SEL_N=0, SRAM /CE=ROM_SEL_N, /OE=SNES /RD, /WE=SNES_WE_N (only if MENU_WE_N=0). BUS_ESP=1 (ESP loads): U9-U11 drive SA*, U12 drives SD* when DOUT_OE_N=0, ROM 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

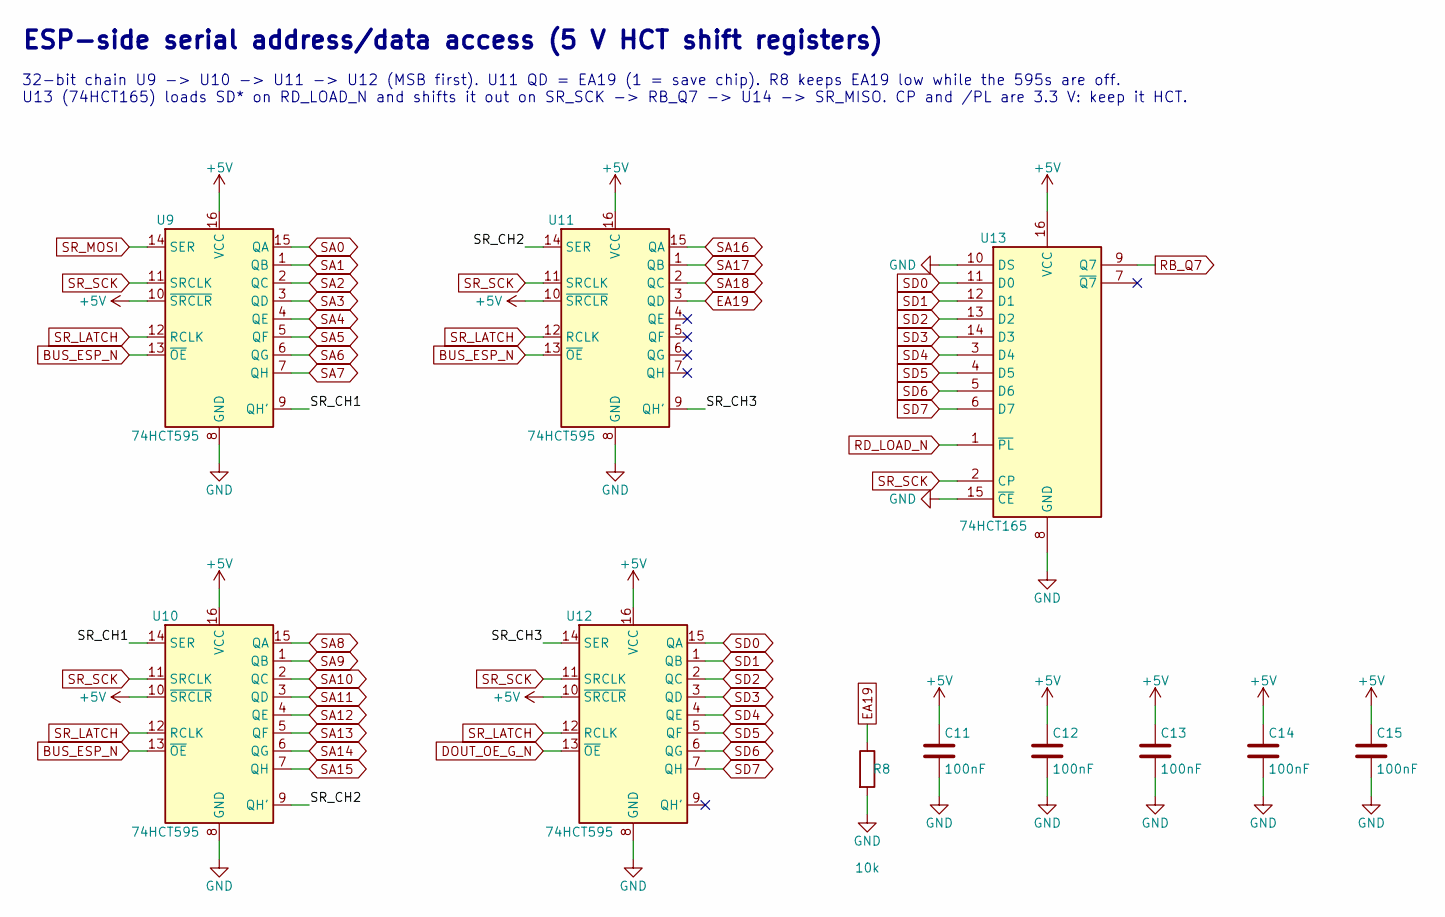
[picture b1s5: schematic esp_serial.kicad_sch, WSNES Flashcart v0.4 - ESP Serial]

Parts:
C11, C12, C13, C14, C15: 100nF; C_0603_1608Metric; MPN CC0603KRX7R9BB104; LCSC C14663
R8: 10k; R_0603_1608Metric; MPN 0603WAF1002T5E; LCSC C25804
U9, U10, U11, U12: 74HCT595; TSSOP-16_4.4x5mm_P0.65mm; MPN 74HCT595PW; LCSC C54411086
U13: 74HCT165; TSSOP-16_4.4x5mm_P0.65mm; MPN SN74HCT165PWR; LCSC C3304572

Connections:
+5V: C11.1, C12.1, C13.1, C14.1, C15.1, U9.10 (~SRCLR), U9.16 (VCC), U10.10 (~SRCLR), U10.16 (VCC), U11.10 (~SRCLR), U11.16 (VCC), U12.10 (~SRCLR), U12.16 (VCC), U13.16 (VCC); also elsewhere on the board
/ESP_Serial/SR_CH1: U9.9 (QH'), U10.14 (SER)
/ESP_Serial/SR_CH2: U10.9 (QH'), U11.14 (SER)
/ESP_Serial/SR_CH3: U11.9 (QH'), U12.14 (SER)
BUS_ESP_N: U9.13 (~OE), U10.13 (~OE), U11.13 (~OE); also elsewhere on the board
DOUT_OE_G_N: U12.13 (~OE); also elsewhere on the board
EA19: R8.1, U11.3 (QD); also elsewhere on the board
GND: C11.2, C12.2, C13.2, C14.2, C15.2, R8.2, U9.8 (GND), U10.8 (GND), U11.8 (GND), U12.8 (GND), U13.8 (GND), U13.10 (DS), U13.15 (~CE); also elsewhere on the board
RB_Q7: U13.9 (Q7); also elsewhere on the board
RD_LOAD_N: U13.1 (~PL); also elsewhere on the board
SA0: U9.15 (QA); also elsewhere on the board
SA1: U9.1 (QB); also elsewhere on the board
SA2: U9.2 (QC); also elsewhere on the board
SA3: U9.3 (QD); also elsewhere on the board
SA4: U9.4 (QE); also elsewhere on the board
SA5: U9.5 (QF); also elsewhere on the board
SA6: U9.6 (QG); also elsewhere on the board
SA7: U9.7 (QH); also elsewhere on the board
SA8: U10.15 (QA); also elsewhere on the board
SA9: U10.1 (QB); also elsewhere on the board
SA10: U10.2 (QC); also elsewhere on the board
SA11: U10.3 (QD); also elsewhere on the board
SA12: U10.4 (QE); also elsewhere on the board
SA13: U10.5 (QF); also elsewhere on the board
SA14: U10.6 (QG); also elsewhere on the board
SA15: U10.7 (QH); also elsewhere on the board
SA16: U11.15 (QA); also elsewhere on the board
SA17: U11.1 (QB); also elsewhere on the board
SA18: U11.2 (QC); also elsewhere on the board
SD0: U12.15 (QA), U13.11 (D0); also elsewhere on the board
SD1: U12.1 (QB), U13.12 (D1); also elsewhere on the board
SD2: U12.2 (QC), U13.13 (D2); also elsewhere on the board
SD3: U12.3 (QD), U13.14 (D3); also elsewhere on the board
SD4: U12.4 (QE), U13.3 (D4); also elsewhere on the board
SD5: U12.5 (QF), U13.4 (D5); also elsewhere on the board
SD6: U12.6 (QG), U13.5 (D6); also elsewhere on the board
SD7: U12.7 (QH), U13.6 (D7); also elsewhere on the board
SR_LATCH: U9.12 (RCLK), U10.12 (RCLK), U11.12 (RCLK), U12.12 (RCLK); also elsewhere on the board
SR_MOSI: U9.14 (SER); also elsewhere on the board
SR_SCK: U9.11 (SRCLK), U10.11 (SRCLK), U11.11 (SRCLK), U12.11 (SRCLK), U13.2 (CP); also elsewhere on the board

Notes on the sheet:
ESP-side serial address/data access (5 V HCT shift registers)
32-bit chain U9 -> U10 -> U11 -> U12 (MSB first). U11 QD = EA19 (1 = save chip). R8 keeps EA19 low while the 595s are off. U13 (74HCT165) loads SD* on RD_LOAD_N and shifts it out on SR_SCK -> RB_Q7 -> U14 -> SR_MISO. CP and /PL are 3.3 V: keep it HCT.

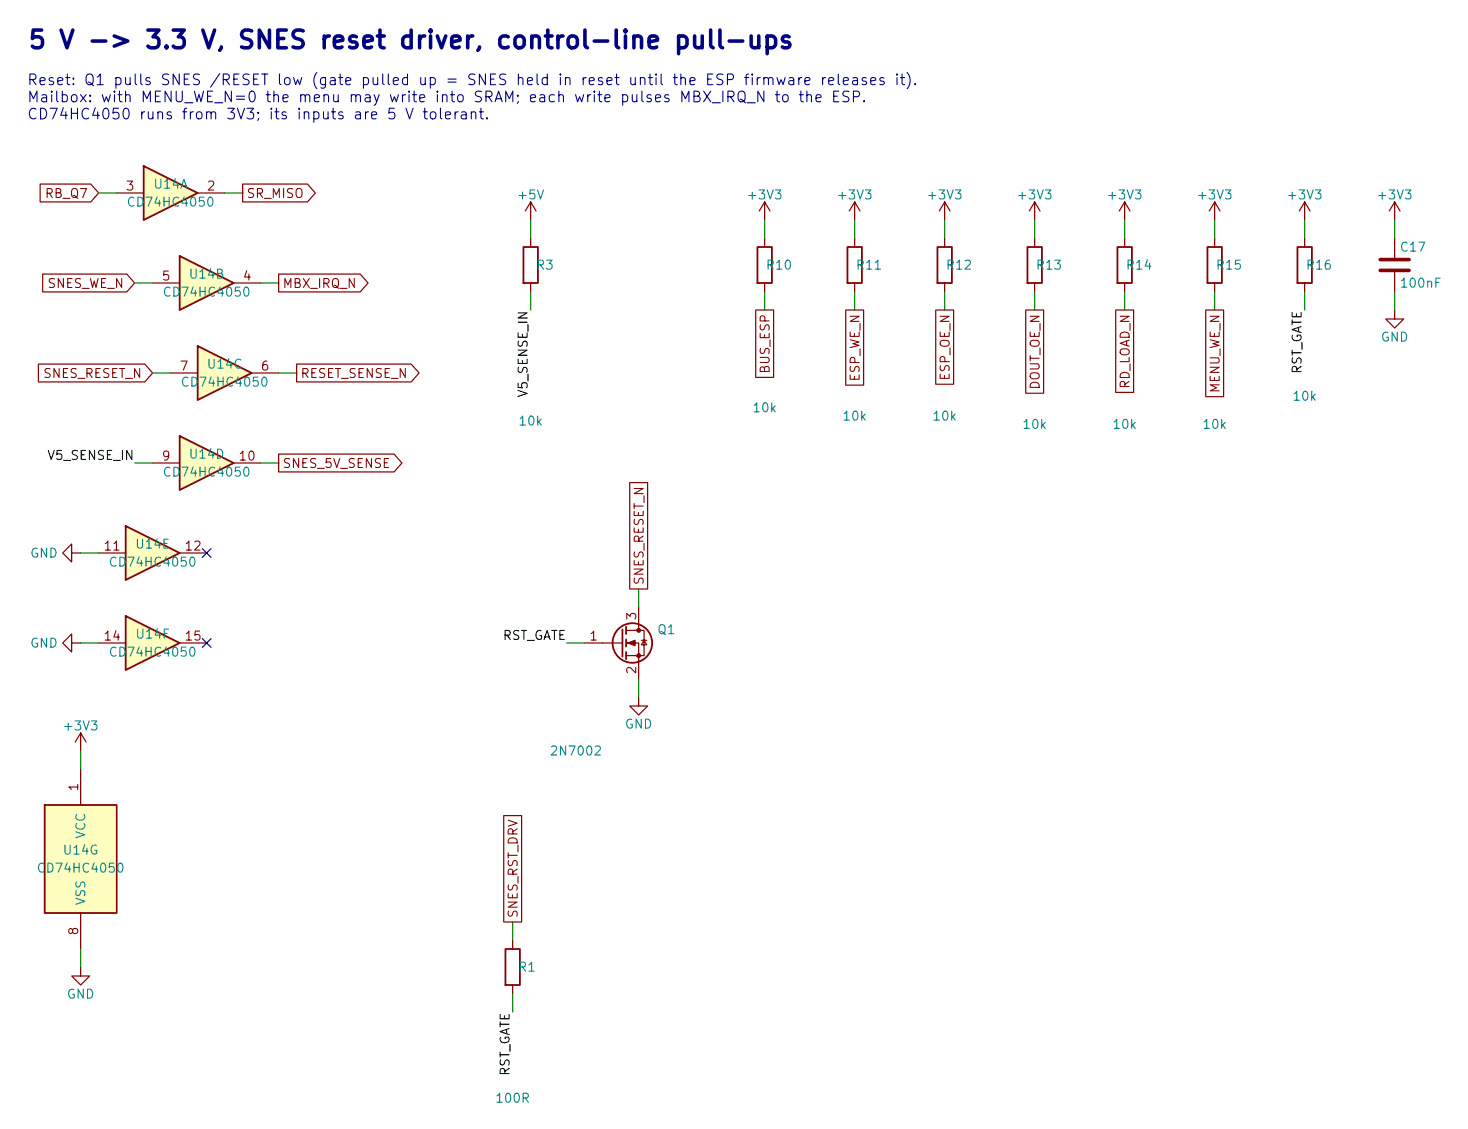
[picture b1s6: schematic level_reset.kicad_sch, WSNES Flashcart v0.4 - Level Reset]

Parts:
C17: 100nF; C_0603_1608Metric; MPN CC0603KRX7R9BB104; LCSC C14663
Q1: 2N7002; SOT-23; MPN 2N7002; LCSC C8545
R1: 100R; R_0603_1608Metric; MPN 0603WAF1000T5E; LCSC C22775
R3, R10, R11, R12, R13, R14, R15, R16: 10k; R_0603_1608Metric; MPN 0603WAF1002T5E; LCSC C25804
U14: CD74HC4050; TSSOP-16_4.4x5mm_P0.65mm; MPN CD74HC4050PWR; LCSC C352825

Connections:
+3V3: C17.1, R10.1, R11.1, R12.1, R13.1, R14.1, R15.1, R16.1, U14.1 (VCC); also elsewhere on the board
+5V: R3.1; also elsewhere on the board
/Level_Reset/RST_GATE: Q1.1 (G), R1.2, R16.2
/Level_Reset/V5_SENSE_IN: R3.2, U14.9
BUS_ESP: R10.2; also elsewhere on the board
DOUT_OE_N: R13.2; also elsewhere on the board
ESP_OE_N: R12.2; also elsewhere on the board
ESP_WE_N: R11.2; also elsewhere on the board
GND: C17.2, Q1.2 (S), U14.8 (VSS), U14.11, U14.14; also elsewhere on the board
MBX_IRQ_N: U14.4; also elsewhere on the board
MENU_WE_N: R15.2; also elsewhere on the board
RB_Q7: U14.3; also elsewhere on the board
RD_LOAD_N: R14.2; also elsewhere on the board
RESET_SENSE_N: U14.6; also elsewhere on the board
SNES_5V_SENSE: U14.10; also elsewhere on the board
SNES_RESET_N: Q1.3 (D), U14.7; also elsewhere on the board
SNES_RST_DRV: R1.1; also elsewhere on the board
SNES_WE_N: U14.5; also elsewhere on the board
SR_MISO: U14.2; also elsewhere on the board

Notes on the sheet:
5 V -> 3.3 V, SNES reset driver, control-line pull-ups
Reset: Q1 pulls SNES /RESET low (gate pulled up = SNES held in reset until the ESP firmware releases it). Mailbox: with MENU_WE_N=0 the menu may write into SRAM; each write pulses MBX_IRQ_N to the ESP. CD74HC4050 runs from 3V3; its inputs are 5 V tolerant.

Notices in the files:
pcb/tools/design.py:
SPDX-License-Identifier: PolyForm-Noncommercial-1.0.0
Copyright 2026 The810man
pcb/WSNES_Proto.kicad_pcb:
Copyright 2026 Paul Maik Rempel aka The810Man (Github user) \
- CC BY-NC-SA 4.0, no commercial use without permission
pcb/WSNES_Proto.kicad_sch:
(c) 2026 The810man - CC BY-NC-SA 4.0, non-commercial
